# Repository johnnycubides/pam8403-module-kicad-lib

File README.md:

# pam8403-module-kicad-lib
Library kicad for pam8403 module

Descargar la librería que contiene el símbolo y el footprint desde aquí [pam8403-kicad-symbol-footprint.zip](./pam8403-kicad-symbol-footprint.zip)

**Símbolo:**

**Footprint:**

Regards Johnny

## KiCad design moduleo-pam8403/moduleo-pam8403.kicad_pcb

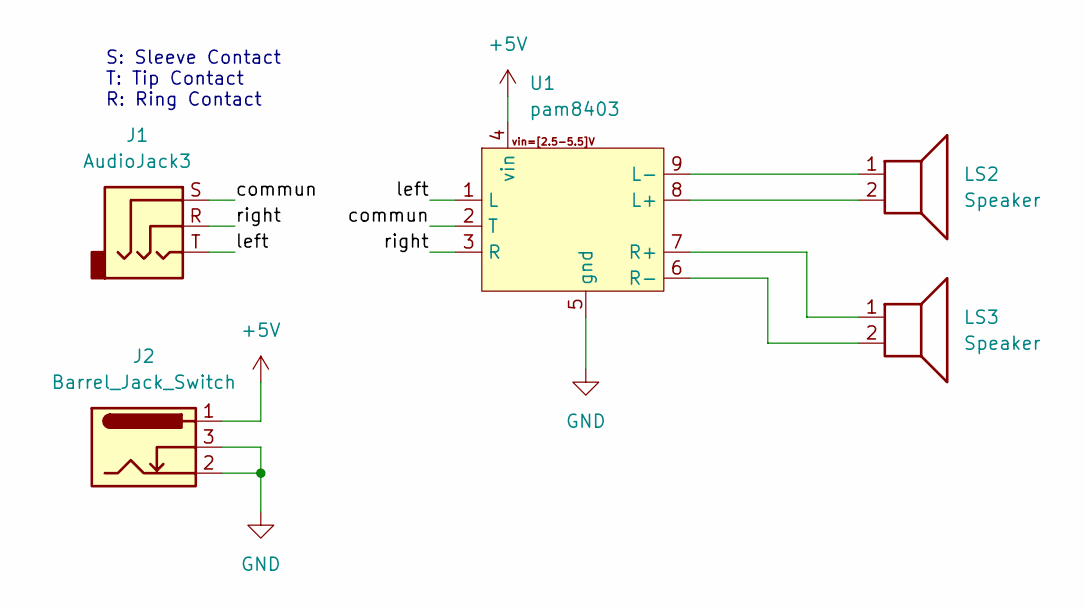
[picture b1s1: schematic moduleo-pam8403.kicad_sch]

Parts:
J1: AudioJack3; Jack_3.5mm_CUI_SJ1-3533NG_Horizontal_CircularHoles
J2: Barrel_Jack_Switch; BarrelJack_Horizontal
LS2, LS3: Speaker; Molex_KK-396_A-41792-0002_1x02_P3.96mm_Horizontal
U1: pam8403

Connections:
+5V: J2.1, U1.4 (vin)
/commun: J1.S, U1.2 (T)
/left: J1.T, U1.1 (L)
/right: J1.R, U1.3 (R)
GND: J2.2, J2.3, U1.5 (gnd)
unnamed: LS3.2, U1.6 (R-)
unnamed: LS3.1, U1.7 (R+)
unnamed: LS2.2, U1.8 (L+)
unnamed: LS2.1, U1.9 (L-)

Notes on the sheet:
S: Sleeve Contact T: Tip Contact R: Ring Contact

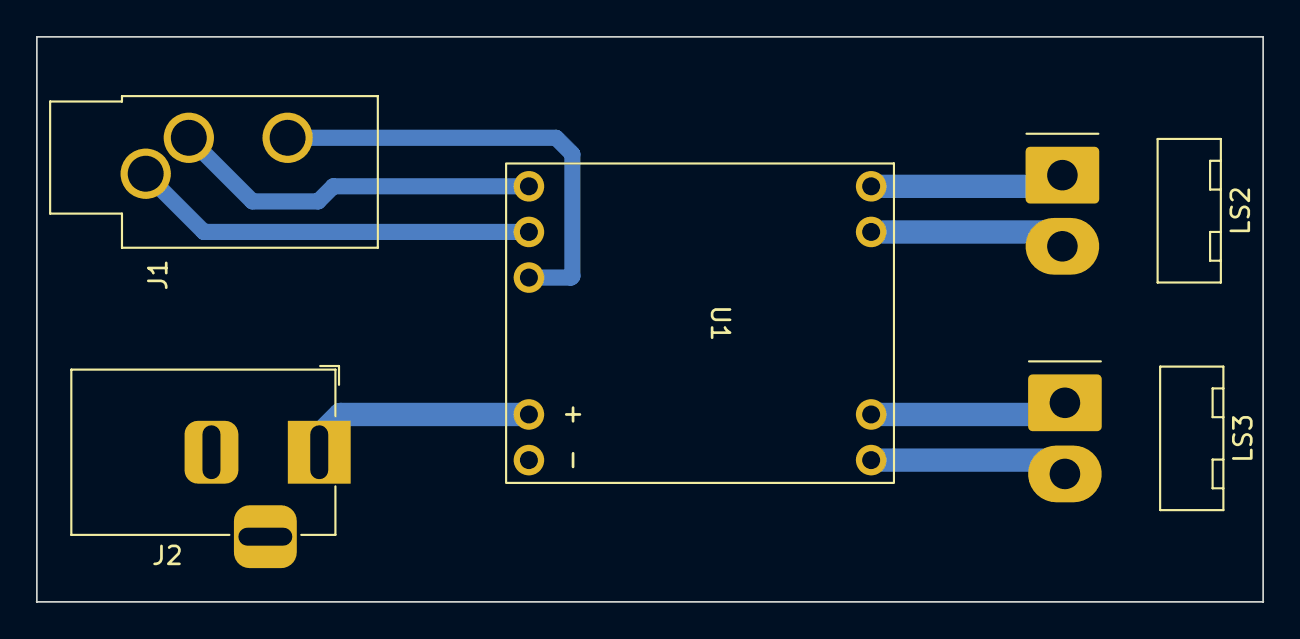
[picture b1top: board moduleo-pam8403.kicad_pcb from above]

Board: 2 copper layers, 68.3 x 31.5 mm, 5 parts (0 on the bottom side), 9 nets.

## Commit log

2023-06-01 add: module
